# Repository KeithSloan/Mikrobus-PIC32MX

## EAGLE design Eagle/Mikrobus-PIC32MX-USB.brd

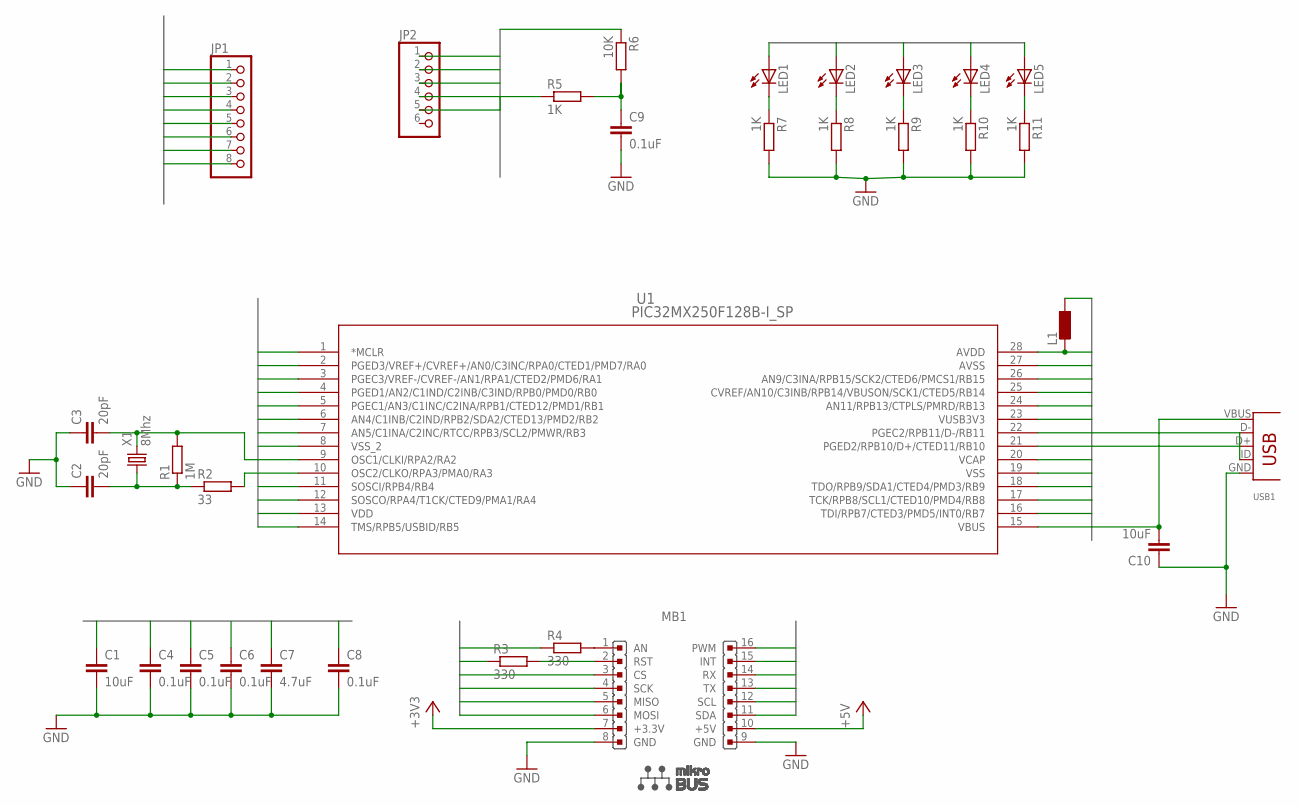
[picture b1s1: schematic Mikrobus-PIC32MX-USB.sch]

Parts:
C1, C10: 10uF; C050-024X044
C2, C3: 20pF; C050-024X044
C4, C5, C6, C8, C9: 0.1uF; C025-024X044
C7: 4.7uF; C050-024X044
JP1: PINHD-1X8; 1X08
JP2: PINHD-1X6; 1X06
L1: L; MLF1608
LED1, LED2, LED3, LED4, LED5: LED1.8MM
MB1: MIKROBUS
R1: 1M; 0204/5
R2: 33; 0204/5
R3, R4: 330; 0204/5
R5, R7, R8, R9, R10, R11: 1K; 0204/5
R6: 10K; 0204/5
U1: PIC32MX250F128B-I_SP; SPDIP28_300MC
USB1: MICRO-USB; USB-WURTH
X1: 8Mhz; HC49

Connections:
+5V: MB1.10 (+5V)
AVDD: C8.1, L1.2, U1.28 (AVDD)
D+: U1.21 (PGED2/RPB10/D+/CTED11/RB10), USB1.ID (D-)
D-: U1.22 (PGEC2/RPB11/D-/RB11), USB1.D+
GND: C1.2, C2.1, C3.1, C4.2, C5.2, C6.2, C7.2, C8.2, C9.2, C10.1, JP1.8, JP2.3, MB1.8 (GND), MB1.9 (GND), R7.2, R8.2, R9.2, R10.2, R11.2, U1.8 (VSS_2), U1.19 (VSS), U1.27 (AVSS), USB1.GND (VBUS)
INT: MB1.15 (INT), U1.14 (TMS/RPB5/USBID/RB5)
LED1: LED1.P1 (A), U1.2 (PGED3/VREF+/CVREF+/AN0/C3INC/RPA0/CTED1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)
LED2: LED2.P1 (A), U1.26 (AN9/C3INA/RPB15/SCK2/CTED6/PMCS1/RB15)
MCLR: JP2.1, R4.1, R5.1, U1.1 (*MCLR)
MISO: MB1.5 (MISO), U1.17 (TCK/RPB8/SCL1/CTED10/PMD4/RB8)
MOSI: JP1.1, MB1.6 (MOSI), U1.3 (PGEC3/VREF-/CVREF-/AN1/RPA1/CTED2/PMD6/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)
unnamed: C2.2, R1.1, R2.1, X1.1
unnamed: MB1.1 (AN), R4.2
unnamed: C9.1, R5.2, R6.2
unnamed: LED1.P2 (C), R7.1
unnamed: LED2.P2 (C), R8.1
unnamed: LED3.P2 (C), R9.1
unnamed: LED4.P2 (C), R10.1
unnamed: MB1.2 (RST), R3.2
unnamed: LED5.P2 (C), R11.1
OSC1: C3.2, R1.2, U1.9 (OSC1/CLKI/RPA2/RA2), X1.2
OSC2: R2.2, U1.10 (OSC2/CLKO/RPA3/PMA0/RA3)
PWM: JP1.6, MB1.16 (PWM), U1.24 (AN11/RPB13/CTPLS/PMRD/RB13)
RA4: JP1.7, U1.12 (SOSCO/RPA4/T1CK/CTED9/PMA1/RA4)
RB4: LED5.P1 (A), U1.11 (SOSCI/RPB4/RB4)
RB9: R3.1, U1.18 (TDO/RPB9/SDA1/CTED4/PMD3/RB9)
RX-PGED: JP1.2
RX/PGED: JP2.4, LED3.P1 (A), MB1.14 (RX), U1.4 (PGED1/AN2/C1IND/C2INB/C3IND/RPB0/PMD0/R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)
SCK: MB1.4 (SCK), U1.25 (CVREF/AN10/C3INB/RPB14/VBUSON/SCK1/CTED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)
SCL: JP1.5, MB1.12 (SCL), U1.7 (AN5/C1INA/C2INC/RTCC/RPB3/SCL2/PMWR/RB3)
SDA: JP1.4, MB1.11 (SDA), U1.6 (AN4/C1INB/C2IND/RPB2/SDA2/CTED13/PMD2/R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)
SS/CS: MB1.3 (CS), U1.16 (TDI/RPB7/CTED3/PMD5/INT0/RB7)
TX-PGEC: JP1.3
TX/PGEC: JP2.5, LED4.P1 (A), MB1.13 (TX), U1.5 (PGEC1/AN3/C1INC/C2INA/RPB1/CTED12/PMD1/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)
VBUS: C10.2, U1.15 (VBUS), USB1.VBUS (GND)
VCAP: C1.1, C4.1, U1.20 (VCAP)
VDD: C5.1, C6.1, C7.1, JP2.2, L1.1, MB1.7 (+3.3V), R6.1, U1.13 (VDD), U1.23 (VUSB3V3)

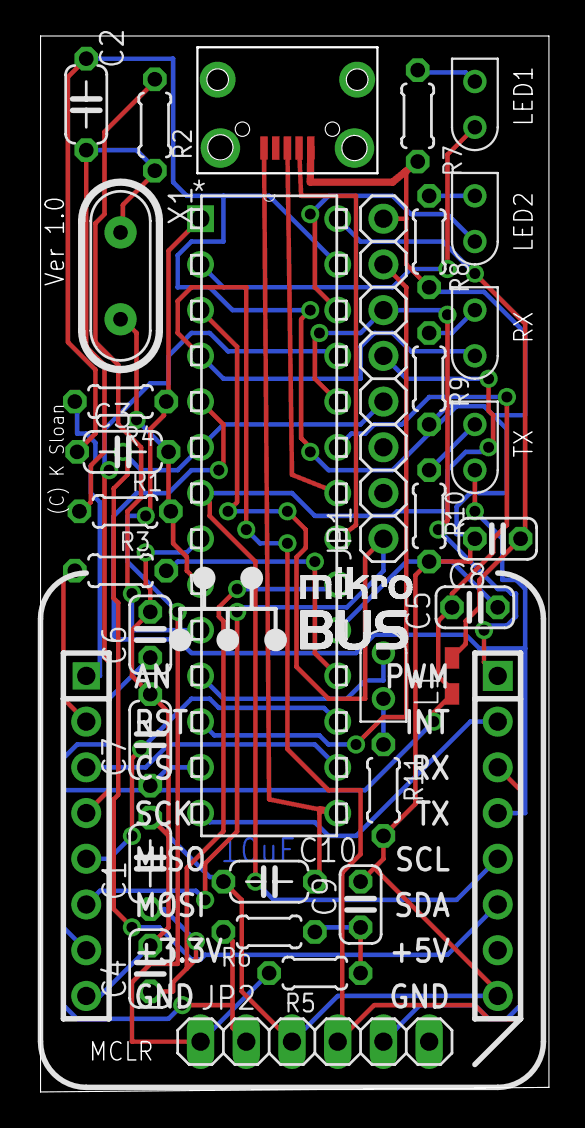
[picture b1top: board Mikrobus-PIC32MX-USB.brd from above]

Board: 2 copper layers, 28.4 x 58.5 mm, 33 parts (0 on the bottom side), 34 nets.

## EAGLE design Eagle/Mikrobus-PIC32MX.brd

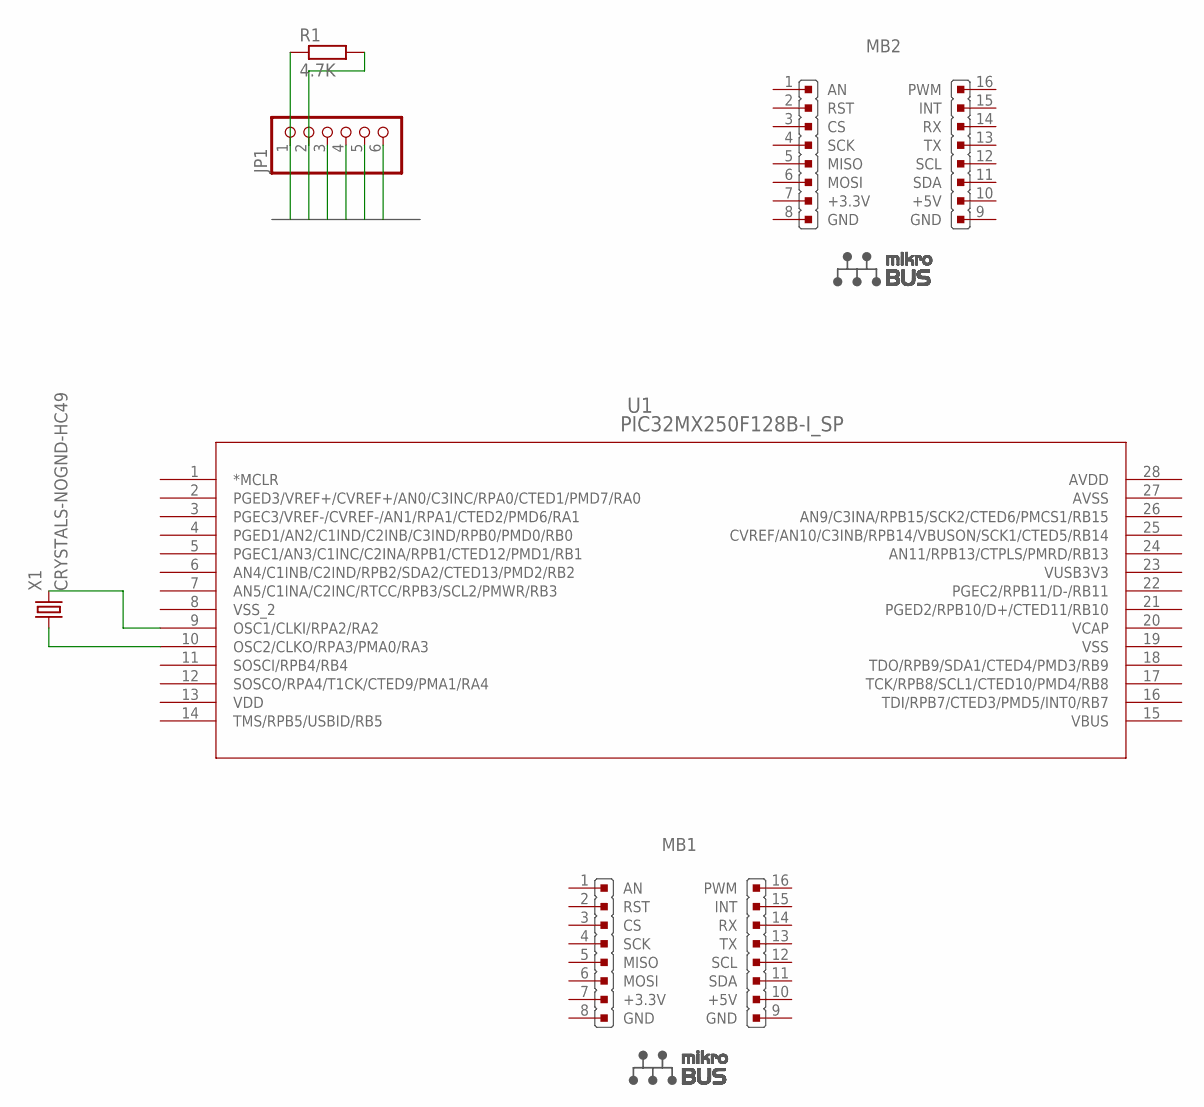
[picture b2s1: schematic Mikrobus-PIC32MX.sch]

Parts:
JP1: PINHD-1X6; 1X06
MB1, MB2: MIKROBUS
R1: 4.7K; 0204/5
U1: PIC32MX250F128B-I_SP; SPDIP28_300MC
X1: CRYSTALS-NOGND-HC49; HC49

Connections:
AVDD: U1.28 (AVDD)
AVSS: U1.27 (AVSS)
MCRL: JP1.1, R1.1
unnamed: U1.9 (OSC1/CLKI/RPA2/RA2), X1.2
unnamed: U1.10 (OSC2/CLKO/RPA3/PMA0/RA3), X1.1
PGC: JP1.5
PGD: JP1.4
PGM: JP1.6
VBUS: U1.15 (VBUS)
VCAP: U1.20 (VCAP)
VDD: JP1.2, R1.2, U1.13 (VDD)
VSS: JP1.3, U1.19 (VSS)
VSS_2: U1.8 (VSS_2)
VUSB3V3: U1.23 (VUSB3V3)

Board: 2 copper layers, 6 parts (0 on the bottom side), 5 nets, no tracks yet.

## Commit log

2016-12-15 Correction USB connector orientation
